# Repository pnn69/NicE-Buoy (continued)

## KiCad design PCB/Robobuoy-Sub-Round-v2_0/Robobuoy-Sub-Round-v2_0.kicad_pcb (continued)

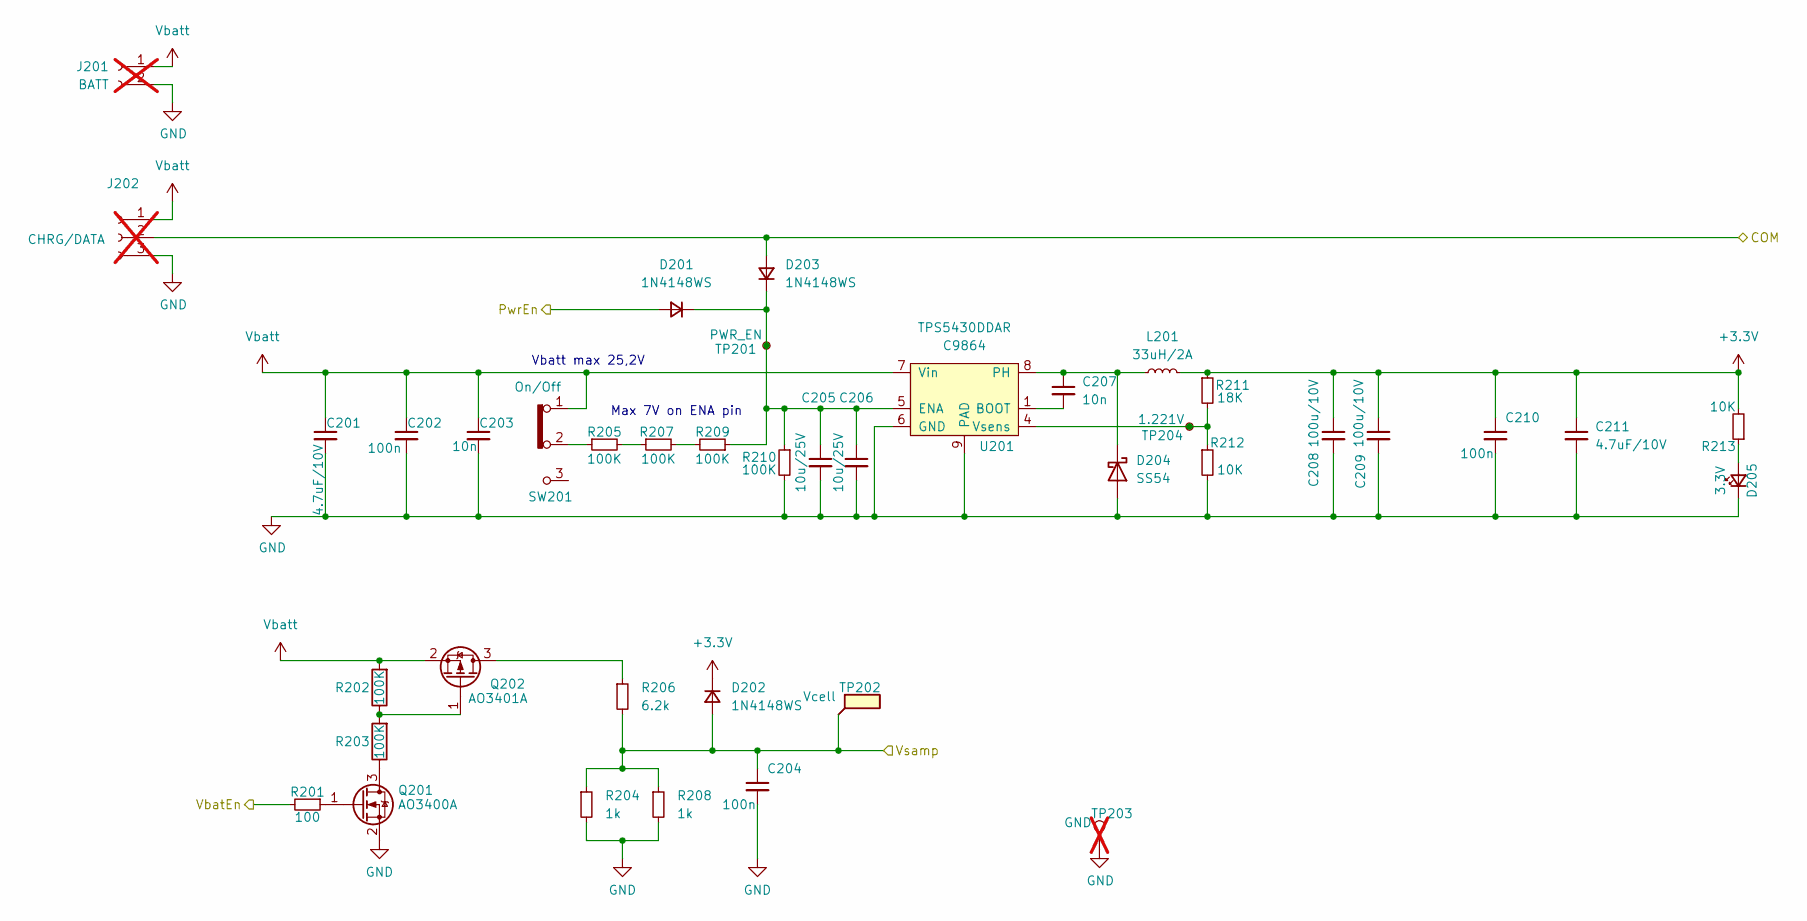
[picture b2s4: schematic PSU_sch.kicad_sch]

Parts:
C201, C211: 4.7uF/10V; C_1206_(1.6); LCSC C29823
C202, C204, C210: 100n; C_0603; LCSC C14663
C203, C207: 10n; C_0603; LCSC C57112
C205, C206: 10u/25V; C_0805; LCSC C15850
C208, C209: 100u/10V; C_1210_3225Metric; LCSC C23742
D201, D202, D203: 1N4148WS; D_SOD-323_1.8x1.4x1.15; LCSC C2128
D204: SS54; D_SMA; LCSC C22452
D205: 3.3V; LED_0805; LCSC C2297
J201: BATT; SolderWire-0.75sqmm_1x02_P4.8mm_D1.25mm_OD2.3mm; not fitted
J202: CHRG/DATA; SolderWire-0.75sqmm_1x03_P4.8mm_D1.25mm_OD2.3mm; not fitted
L201: 33uH/2A; L_6.6x7.0mm; LCSC C177245
Q201: AO3400A; SOT-23; LCSC C20917
Q202: AO3401A; SOT-23; LCSC C15127
R201: 100; R_0603; LCSC C22775
R202, R203: 100K; R_0603; Farnell 2331736
R204, R208: 1k; R_0603; LCSC C21190
R205, R207, R209, R210: 100K; R_0603; LCSC C25804
R206: 6.2k; R_0603; LCSC C25804
R211: 18K; R_0603; LCSC C25810
R212, R213: 10K; R_0603; LCSC C25804
SW201: On/Off; Header_1x03_P2.54_Male; LCSC C2937625
TP201: PWR_EN; Testpad_1
TP202: Vcell; Testpad_1
TP203: GND; TestPoint_Loop_D2.54mm_Drill1.5mm_Beaded; not fitted
TP204: 1.221V; Testpad_1
U201: TPS5430DDAR; HTSOP-8-1EP_3.9x4.9mm_P1.27mm_EP2.4x3.2mm_ThermalVias; LCSC C9864

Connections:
+3.3V: C208.1, C209.1, C210.1, C211.1, D202.1 (K), L201.2, R211.1, R213.2; also elsewhere on the board
/CPU/COM: D203.2 (A), J202.2; also elsewhere on the board
/CPU/PwrEn: D201.2 (A); also elsewhere on the board
/CPU/VbatEn: R201.2; also elsewhere on the board
/CPU/Vsamp: C204.1, D202.2 (A), R204.1, R206.2, R208.1, TP202.1; also elsewhere on the board
GND: C201.2, C202.2, C203.2, C204.2, C205.2, C206.2, C208.2, C209.2, C210.2, C211.2, D204.2 (A), D205.1 (K), J201.2, J202.3, Q201.2 (S), R204.2, R208.2, R210.2, R212.2, TP203.1, U201.6 (GND), U201.9 (PAD); also elsewhere on the board
unnamed: C205.1, C206.1, D201.1 (K), D203.1 (K), R209.1, R210.1, TP201.1, U201.5 (ENA)
unnamed: C207.1, D204.1 (K), L201.1, U201.8 (PH)
unnamed: D205.2 (A), R213.1
unnamed: Q201.3 (D), R203.1
unnamed: Q201.1 (G), R201.1
unnamed: Q202.3 (D), R206.1
unnamed: Q202.1 (G), R202.1, R203.2
unnamed: R205.1, SW201.2
unnamed: R205.2, R207.1
unnamed: R207.2, R209.2
unnamed: C207.2, U201.1 (BOOT)
unnamed: R211.2, R212.1, TP204.1, U201.4 (Vsens)
Vbatt: C201.1, C202.1, C203.1, J201.1, J202.1, Q202.2 (S), R202.2, SW201.1, U201.7 (Vin); also elsewhere on the board

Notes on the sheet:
Vbatt max 25,2V
Max 7V on ENA pin

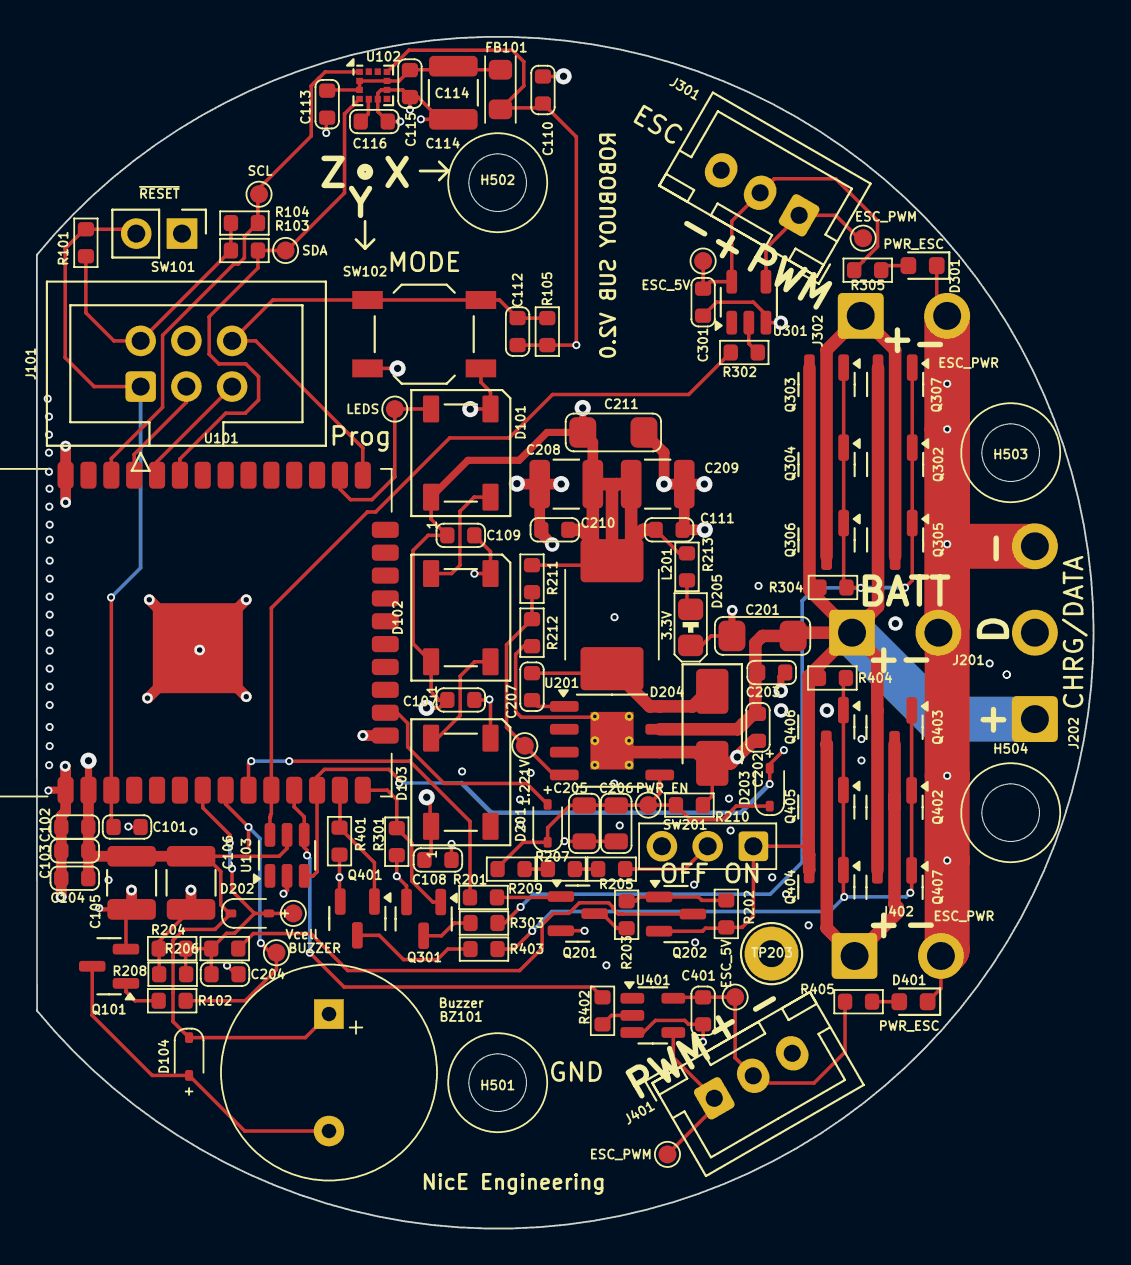
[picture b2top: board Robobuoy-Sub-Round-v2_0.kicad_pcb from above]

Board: 4 copper layers, 58.7 x 66.2 mm, 120 parts (0 on the bottom side), 51 nets.

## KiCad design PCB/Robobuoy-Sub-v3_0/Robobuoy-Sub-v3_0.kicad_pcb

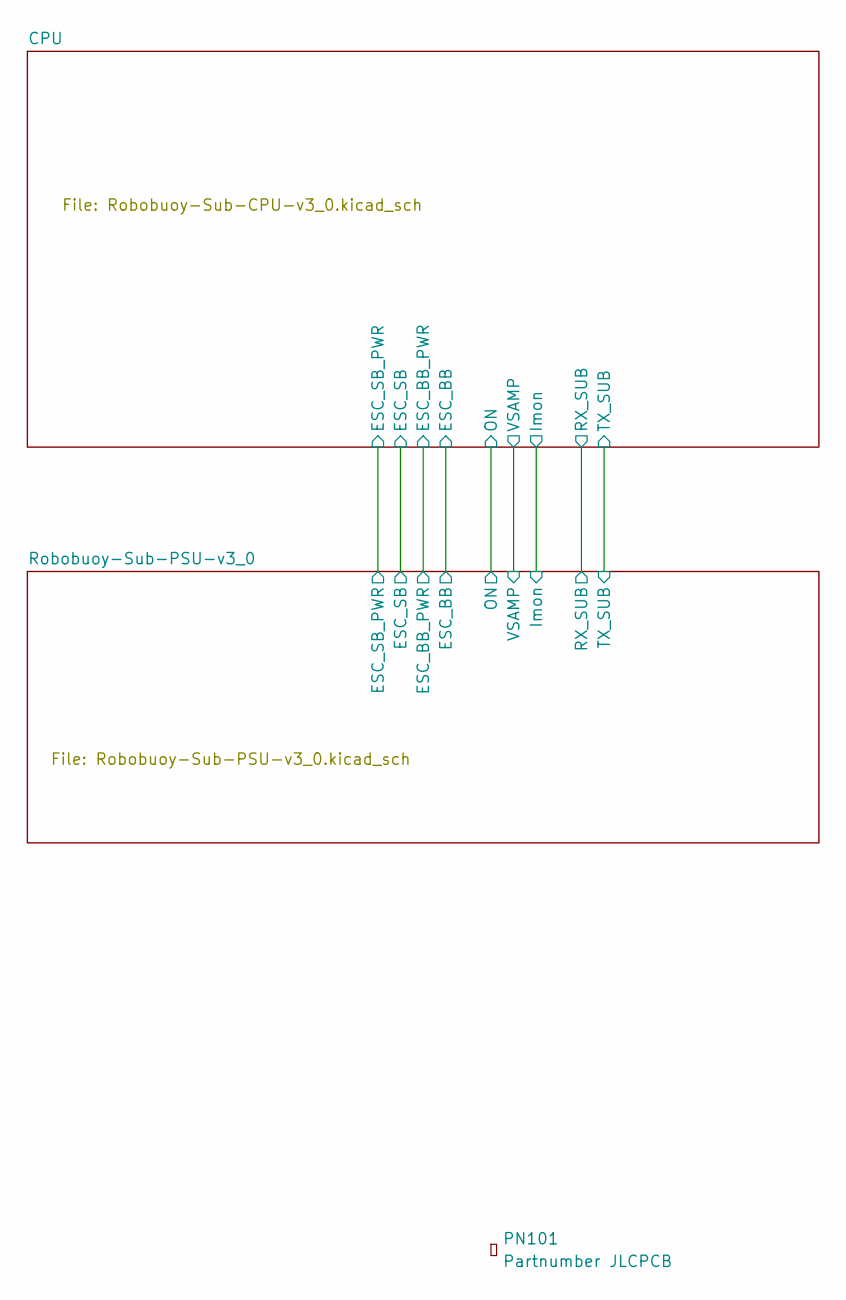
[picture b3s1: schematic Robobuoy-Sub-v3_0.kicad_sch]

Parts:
PN101: Partnumber JLCPCB; Part_Num_JLCPCB

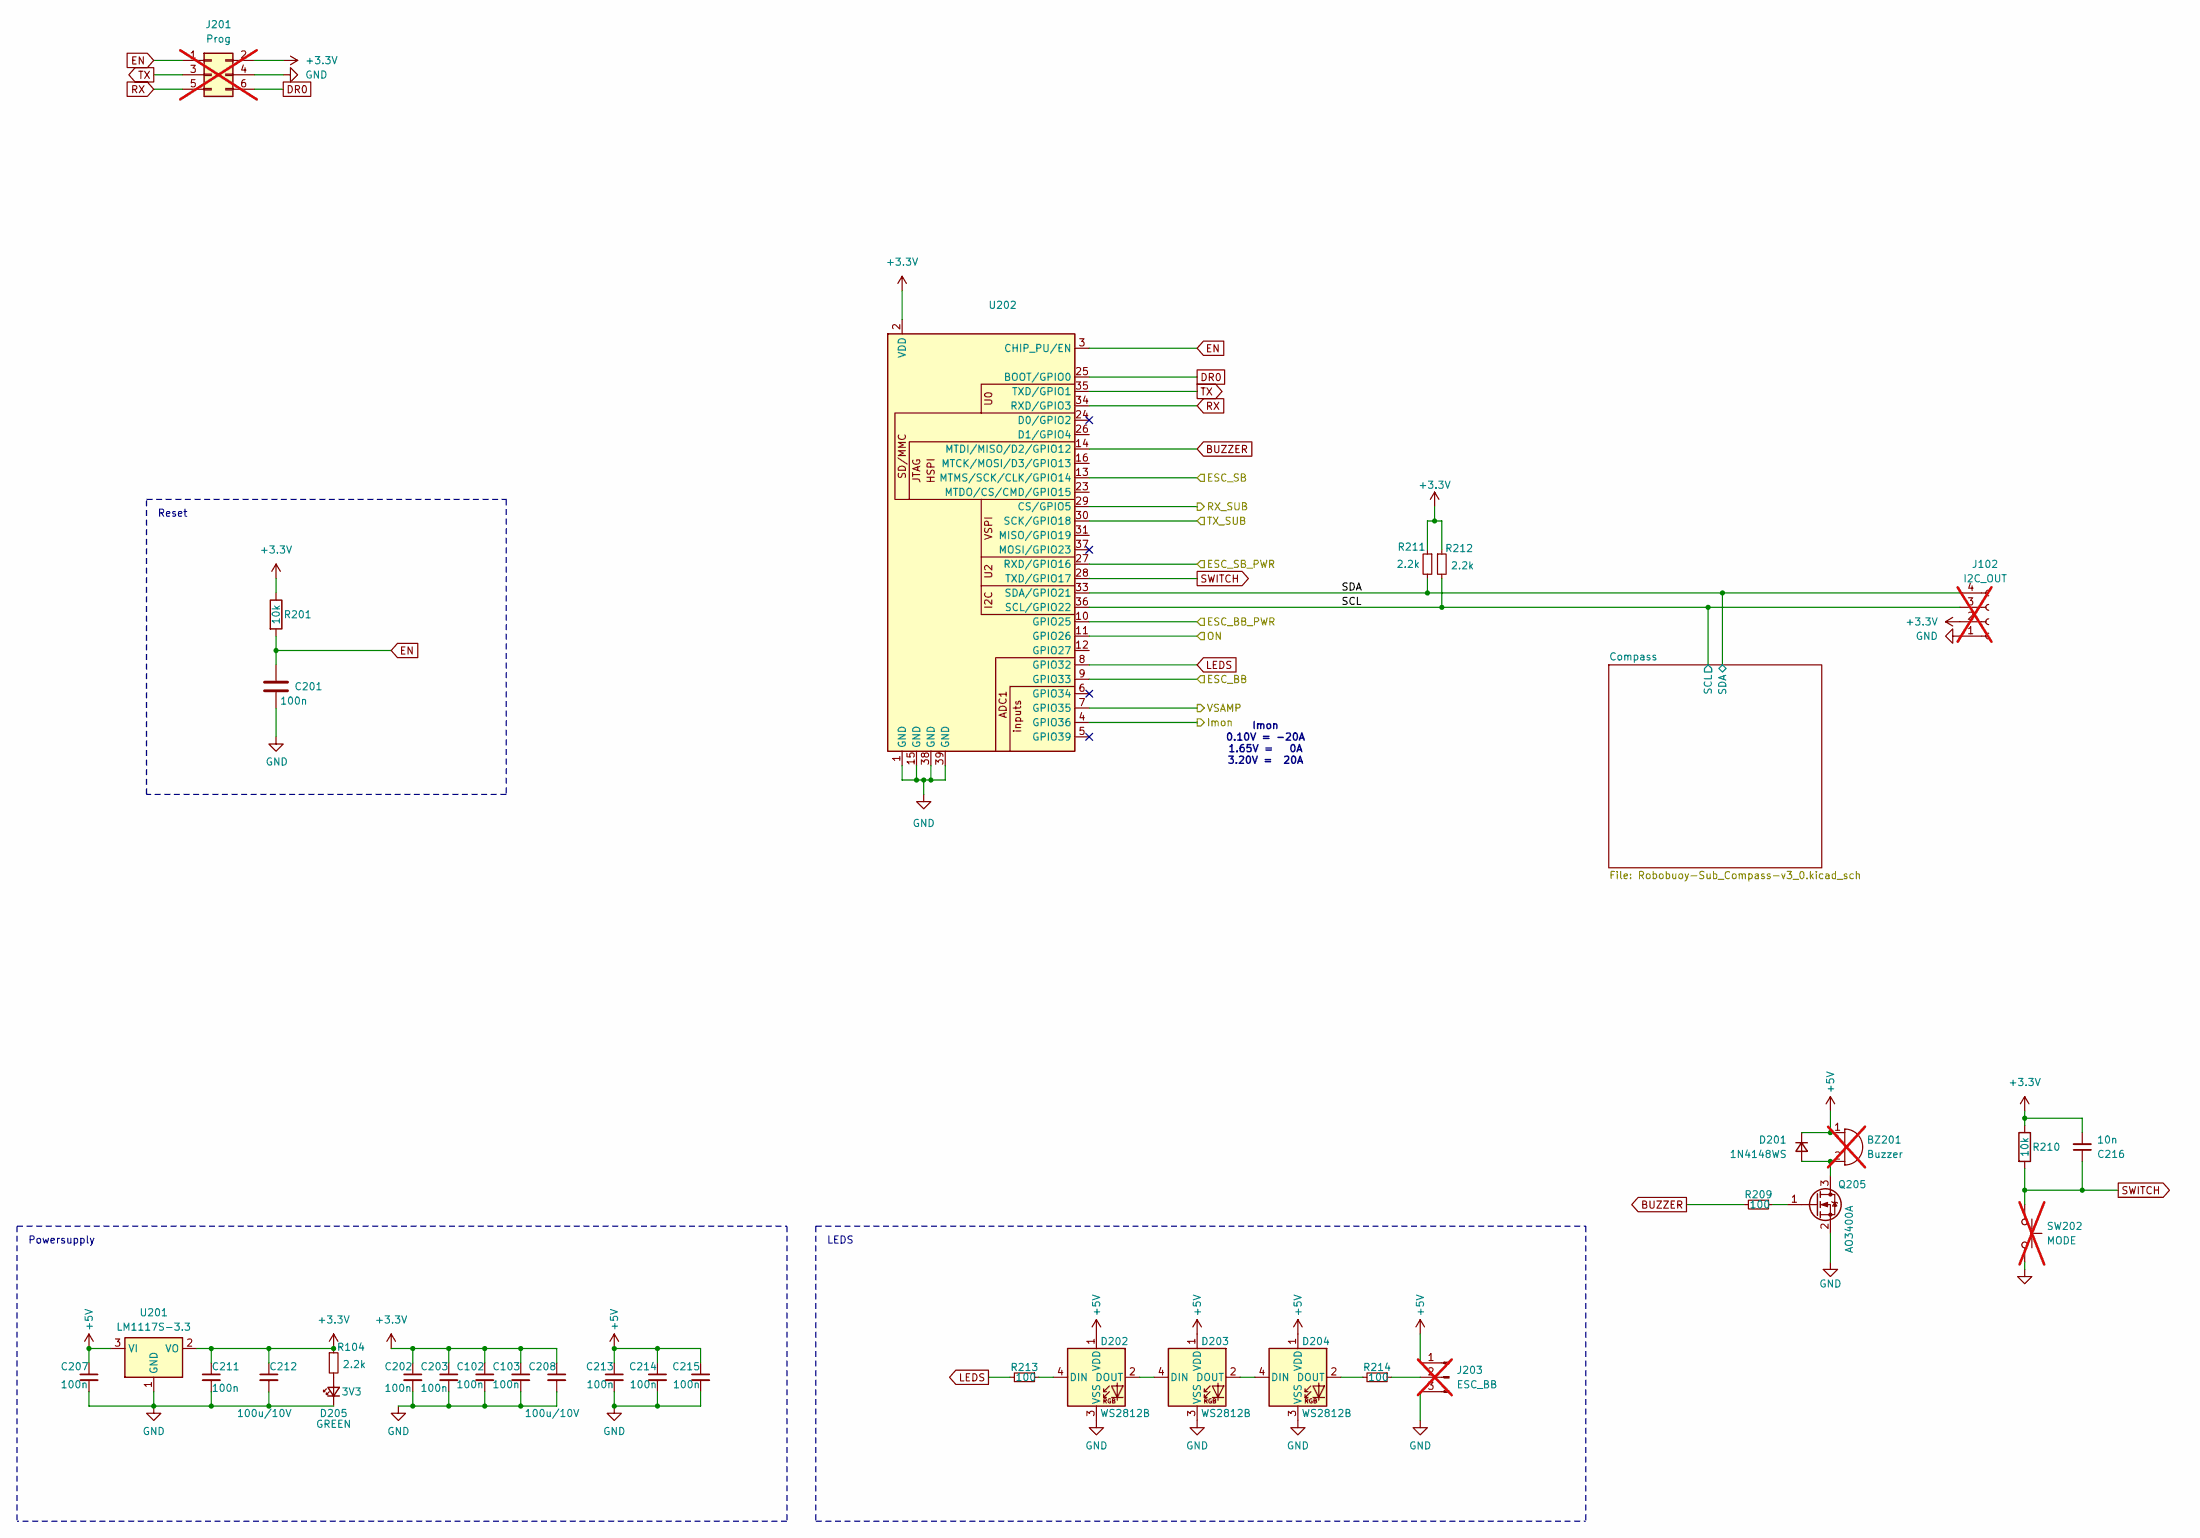
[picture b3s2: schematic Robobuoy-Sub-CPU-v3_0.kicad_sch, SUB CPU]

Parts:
BZ201: Buzzer; Header_1x02_P2.54_Jumper; LCSC C968749; not fitted
C102, C103, C201, C202, C203, C207, C211, C213, C214, C215: 100n; C_0603; LCSC C14663
C208, C212: 100u/10V; C_1210_3225Metric; LCSC C23742
C216: 10n; C_0603; LCSC C57112
D201: 1N4148WS; D_SOD-323_1.8x1.4x1.15; LCSC C2128
D202, D203, D204: WS2812B; LED_WS2812B_PLCC4_5.0x5.0mm_P3.2mm; LCSC C2843785
D205: GREEN; LED_0603_1608Metric; LCSC C12624
J102: I2C_OUT; Header_1x04_P2.54_Male; not fitted
J201: Prog; IDC-Header_2x03_P2.54mm_Vertical; LCSC C11214; not fitted
J203: ESC_BB; Header_1x03_P2.54_Male; LCSC C5341202; not fitted
Q205: AO3400A; SOT-23; LCSC C20917
R104, R211, R212: 2.2k; R_0603; LCSC C4190
R201, R210: 10k; R_0603; Farnell 2331736
R209, R213, R214: 100; R_0603; LCSC C22775
SW202: MODE; Header_1x02_P2.54_Jumper; not fitted
U201: LM1117S-3.3; SOT223; LCSC C126027
U202: ESP32-WROOM-32E_(visible_peripherals); ESP32-WROOM-32; LCSC C82899

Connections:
+3.3V: C102.1, C103.1, C202.1, C203.1, C208.1, C211.1, C212.1, C216.2, J102.2, J201.2, R104.1, R201.1, R210.1, R211.1, R212.1, U201.2 (VO), U202.2 (VDD); also elsewhere on the board
+5V: BZ201.1 (+), C207.1, C213.1, C214.1, C215.1, D201.1 (K), D202.1 (VDD), D203.1 (VDD), D204.1 (VDD), J203.1, U201.3 (VI); also elsewhere on the board
/CPU/ESC_BB: U202.9 (GPIO33); also elsewhere on the board
/CPU/ESC_BB_PWR: U202.10 (GPIO25); also elsewhere on the board
/CPU/ESC_SB: U202.13 (MTMS/SCK/CLK/GPIO14); also elsewhere on the board
/CPU/ESC_SB_PWR: U202.27 (RXD/GPIO16); also elsewhere on the board
/CPU/Imon: U202.4 (GPIO36); also elsewhere on the board
/CPU/ON: U202.11 (GPIO26); also elsewhere on the board
/CPU/RX_SUB: U202.29 (CS/GPIO5); also elsewhere on the board
/CPU/SCL: J102.3, R212.2, U202.36 (SCL/GPIO22); also elsewhere on the board
/CPU/SDA: J102.4, R211.2, U202.33 (SDA/GPIO21); also elsewhere on the board
/CPU/TX_SUB: U202.30 (SCK/GPIO18); also elsewhere on the board
/CPU/VSAMP: U202.7 (GPIO35); also elsewhere on the board
BUZZER: R209.2, U202.14 (MTDI/MISO/D2/GPIO12)
DR0: J201.6, U202.25 (BOOT/GPIO0)
EN: C201.1, J201.1, R201.2, U202.3 (CHIP_PU/EN)
GND: C102.2, C103.2, C201.2, C202.2, C203.2, C207.2, C208.2, C211.2, C212.2, C213.2, C214.2, C215.2, D202.3 (VSS), D203.3 (VSS), D204.3 (VSS), D205.1 (K), J102.1, J201.4, J203.3, Q205.2 (S), SW202.1, U201.1 (GND), U202.1 (GND), U202.15 (GND), U202.38 (GND), U202.39 (GND); also elsewhere on the board
LEDS: R213.2, U202.8 (GPIO32)
unnamed: BZ201.2 (-), D201.2 (A), Q205.3 (D)
unnamed: D202.4 (DIN), R213.1
unnamed: D202.2 (DOUT), D203.4 (DIN)
unnamed: D203.2 (DOUT), D204.4 (DIN)
unnamed: D204.2 (DOUT), R214.2
unnamed: D205.2 (A), R104.2
unnamed: J203.2, R214.1
unnamed: Q205.1 (G), R209.1
RX: J201.5, U202.34 (RXD/GPIO3)
SWITCH: C216.1, R210.2, SW202.2, U202.28 (TXD/GPIO17)
TX: J201.3, U202.35 (TXD/GPIO1)

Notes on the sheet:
Reset
Imon 0.10V = -20A 1.65V = 0A 3.20V = 20A
Powersupply
LEDS

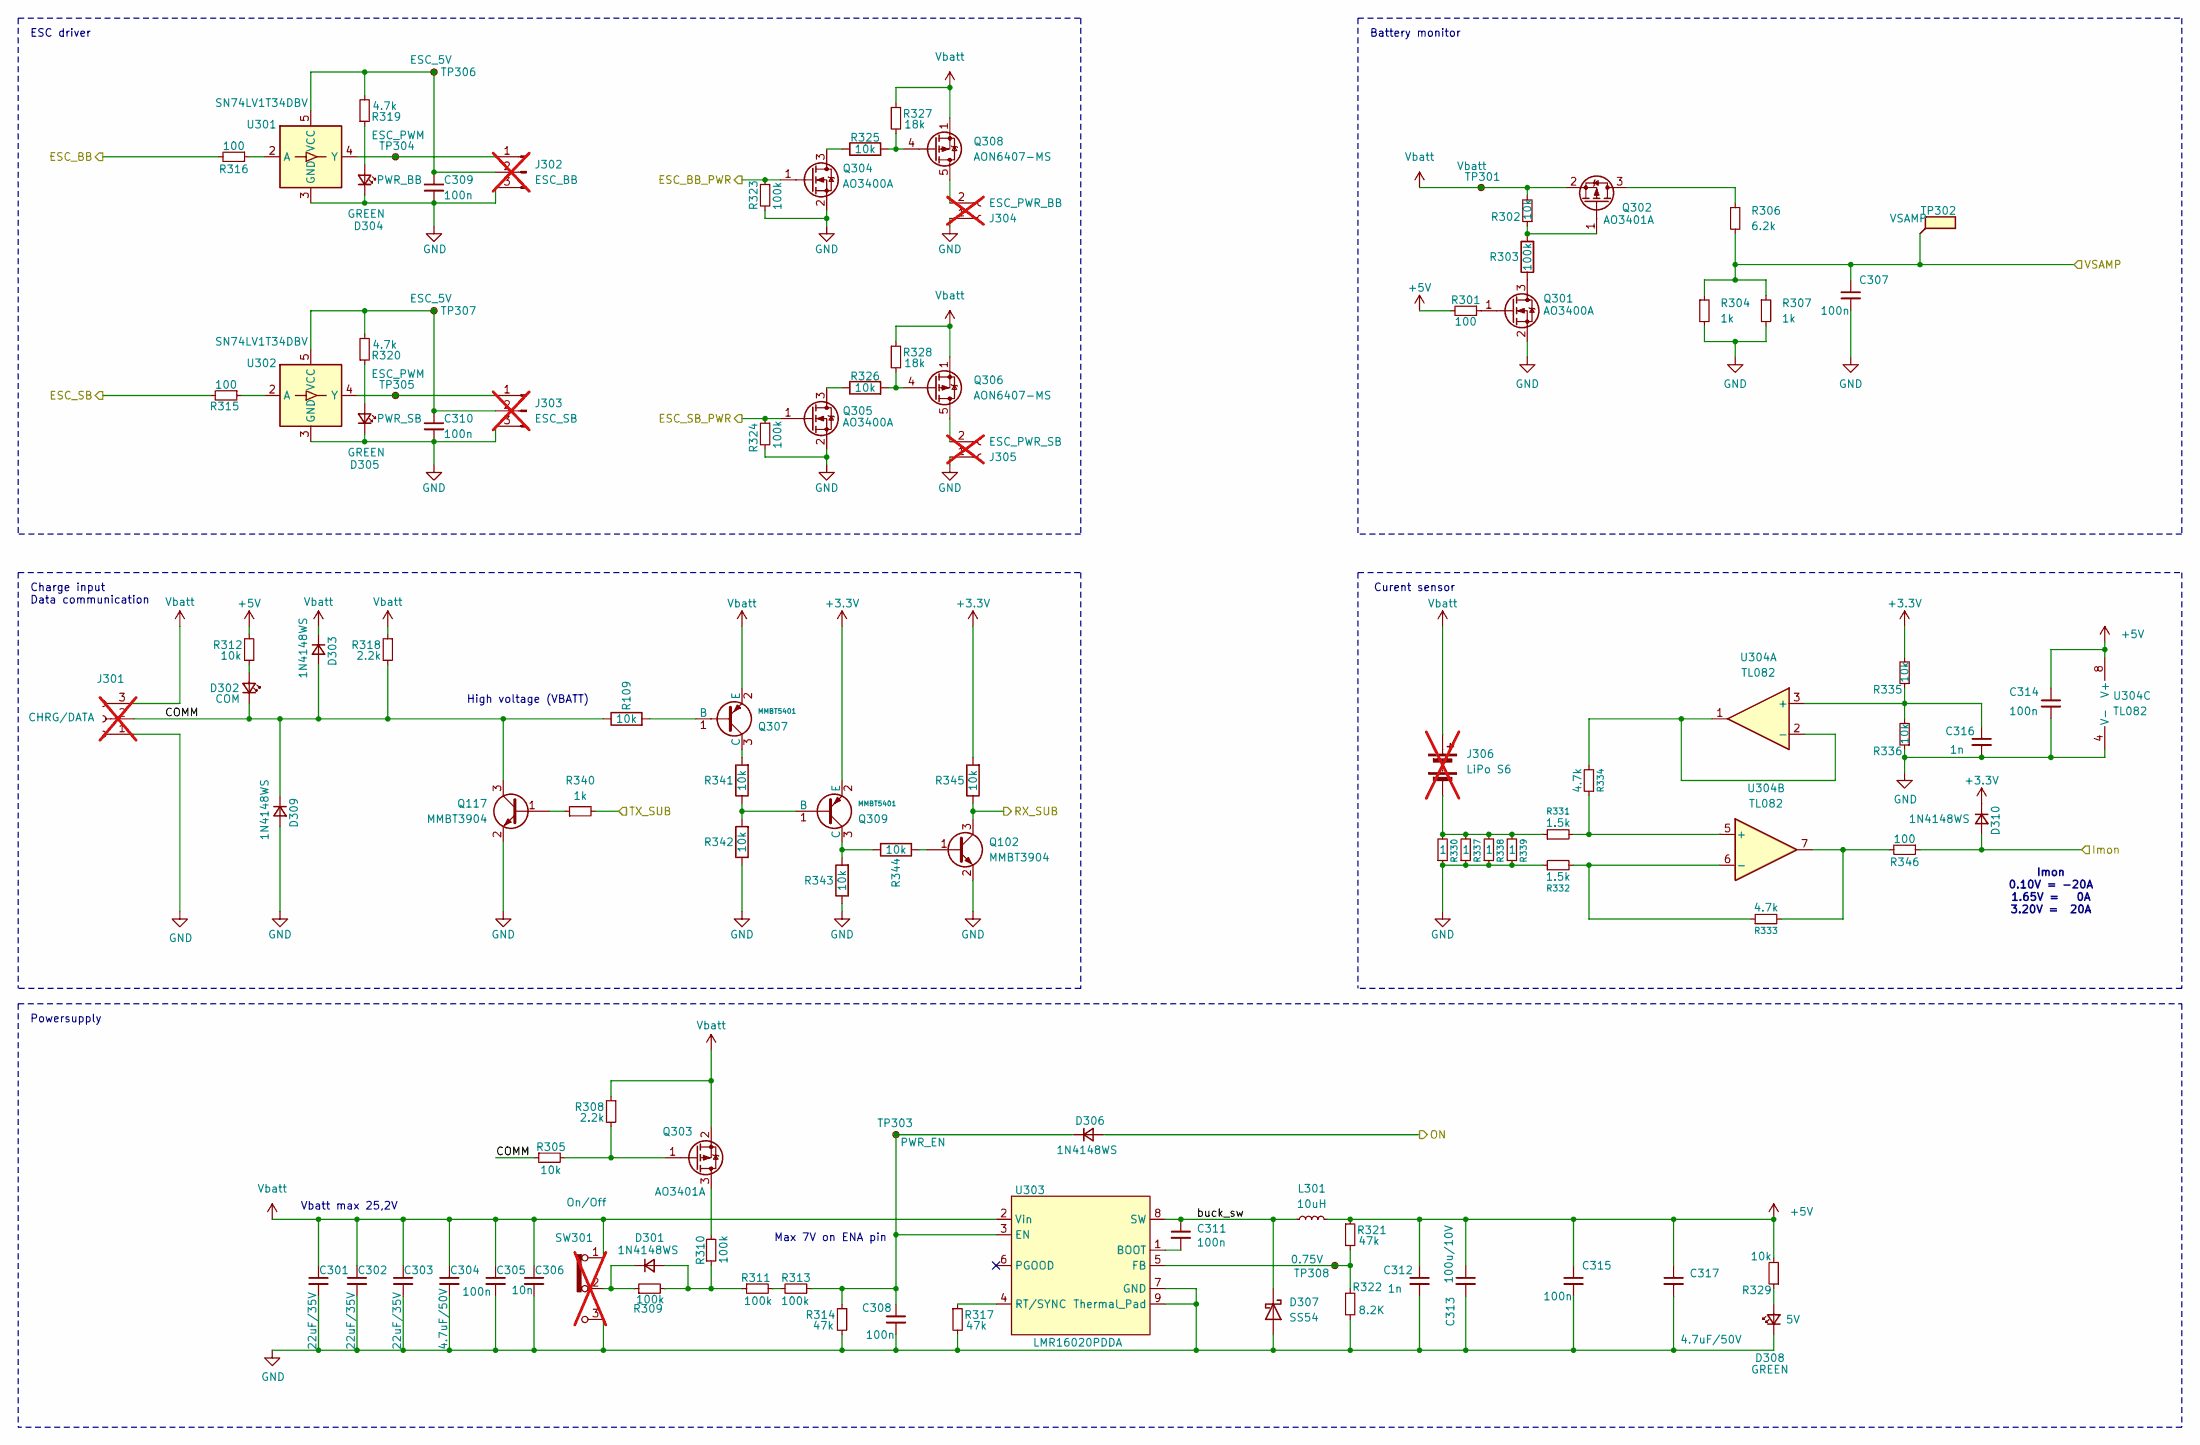
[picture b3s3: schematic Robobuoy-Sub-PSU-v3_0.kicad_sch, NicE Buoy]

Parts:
C301, C302, C303: 22uF/35V; C_1206_3216Metric; LCSC C6119969
C304, C317: 4.7uF/50V; C_1206_3216Metric; LCSC C29823
C305, C307, C308, C309, C310, C311, C314, C315: 100n; C_0603; LCSC C14663
C306: 10n; C_0603; LCSC C57112
C312, C316: 1n; C_0603; LCSC C1588
C313: 100u/10V; C_1210_3225Metric; LCSC C23742
D301, D303, D306, D309, D310: 1N4148WS; D_SOD-323_1.8x1.4x1.15; LCSC C2128
D302: COM; LED_0603_1608Metric; LCSC C2286
D304, D305, D308: GREEN; LED_0603_1608Metric; LCSC C12624
D307: SS54; D_SMA; LCSC C22452
J301: CHRG/DATA; RoundWire_1x03_P5.50mm_Vertical; LCSC C19268044; not fitted
J302: ESC_BB; JST_XH_B3B-XH-A_1x03_P2.50mm_Vertical; LCSC C5341202; not fitted
J303: ESC_SB; JST_XH_B3B-XH-A_1x03_P2.50mm_Vertical; LCSC C5341202; not fitted
J304: ESC_PWR_BB; AMASS_XT30U-M_1x02_P5.0mm_Vertical; LCSC C428722; not fitted
J305: ESC_PWR_SB; AMASS_XT30U-M_1x02_P5.0mm_Vertical; LCSC C428722; not fitted
J306: LiPo S6; not fitted
L301: 10uH; L_6.6x7.0mm; LCSC C2894722
Q102, Q117: MMBT3904; SOT-23
Q301, Q304, Q305: AO3400A; SOT-23; LCSC C20917
Q302, Q303: AO3401A; SOT-23; LCSC C15127
Q306, Q308: AON6407-MS; AO_DFN-8-1EP_5.55x5.2mm_P1.27mm_EP4.12x4.6mm; LCSC C17702953
Q307, Q309: MMBT5401; Q_SOT-23; Part MMBT5401; LCSC C7420356
R109, R341, R342, R343, R344, R345: 10k; R_0603; Farnell 2331736
R301, R315, R316, R346: 100; R_0603; LCSC C22775
R302, R305, R312, R325, R326, R329, R335, R336: 10k; R_0603; LCSC C25804
R303, R309, R310, R311, R313, R323, R324: 100k; R_0603; LCSC C25803
R304, R307, R340: 1k; R_0603; LCSC C21190
R306: 6.2k; R_0603; LCSC C4260
R308, R318: 2.2k; R_0603; LCSC C4190
R314, R317, R321: 47k; R_0603; LCSC C25819
R319, R320, R333, R334: 4.7k; R_0603; LCSC C4177
R322: 8.2K; R_0603; LCSC C25981
R327, R328: 18k; R_0603; LCSC C25810
R330, R337, R338, R339: 1; R_2512_6332Metric_Pad1.40x3.35mm_HandSolder
R331, R332: 1.5k; R_0603
SW301: On/Off; Header_1x03_P2.54_Male; LCSC C2937625; not fitted
TP301: Vbatt; Testpad_1.4
TP302: VSAMP; Testpad_1
TP303: PWR_EN; Testpad_1.4
TP304: ESC_PWM; Testpad_1
TP305: ESC_PWM; Testpad_1.4
TP306: ESC_5V; Testpad_1
TP307: ESC_5V; Testpad_1.4
TP308: 0.75V; Testpad_1.4
U301, U302: SN74LV1T34DBV; SOT-23-5; LCSC C100024
U303: LMR16020PDDA; SOIC-8-1EP_3.9x4.9mm_P1.27mm_EP2.41x3.81mm_ThermalVias; LCSC C190006
U304: TL082; SO-8_3.9x4.9mm_P1.27mm

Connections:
+3.3V: D310.1 (K), Q309.2 (E), R335.2, R345.2; also elsewhere on the board
+5V: C312.1, C313.1, C314.1, C315.1, C317.1, L301.2, R301.2, R312.2, R321.1, R329.2, U304.8 (V+); also elsewhere on the board
/CPU/ESC_BB: R316.2; also elsewhere on the board
/CPU/ESC_BB_PWR: Q304.1 (G), R323.1; also elsewhere on the board
/CPU/ESC_SB: R315.2; also elsewhere on the board
/CPU/ESC_SB_PWR: Q305.1 (G), R324.1; also elsewhere on the board
/CPU/Imon: D310.2 (A), R346.1; also elsewhere on the board
/CPU/ON: D306.2 (A); also elsewhere on the board
/CPU/RX_SUB: Q102.3 (C), R345.1; also elsewhere on the board
/CPU/TX_SUB: R340.2; also elsewhere on the board
/CPU/VSAMP: C307.1, R304.1, R306.2, R307.1, TP302.1; also elsewhere on the board
/Robobuoy-Sub-PSU-v3_0/COMM: D302.1 (K), D303.2 (A), D309.1 (K), J301.2, Q117.3 (C), R109.1, R305.1, R318.2
/Robobuoy-Sub-PSU-v3_0/buck_sw: C311.1, D307.1 (K), L301.1, U303.8 (SW)
GND: C301.2, C302.2, C303.2, C304.2, C305.2, C306.2, C307.2, C308.2, C309.2, C310.2, C312.2, C313.2, C314.2, C315.2, C316.2, C317.2, D304.1 (K), D305.1 (K), D307.2 (A), D308.1 (K), D309.2 (A), J301.1, J302.3, J303.3, J304.1, J305.1, Q102.2 (E), Q117.2 (E), Q301.2 (S), Q304.2 (S), Q305.2 (S), R304.2, R307.2, R314.2, R317.2, R322.2, R323.2, R324.2, R330.1, R332.1, R336.1, R337.1, R338.1, R339.1, R342.1, R343.1, SW301.3, U301.3 (GND), U302.3 (GND), U303.7 (GND), U303.9 (Thermal_Pad), U304.4 (V-); also elsewhere on the board
unnamed: D301.2 (A), R309.2, R310.1, R311.1
unnamed: D301.1 (K), R309.1, SW301.2
unnamed: D302.2 (A), R312.1
unnamed: D304.2 (A), R319.1
unnamed: D305.2 (A), R320.1
unnamed: C308.1, D306.1 (K), R313.1, R314.1, TP303.1, U303.3 (EN)
unnamed: D308.2 (A), R329.1
unnamed: J302.1, TP304.1, U301.4 (Y)
unnamed: C309.1, J302.2, R319.2, TP306.1, U301.5 (VCC)
unnamed: J303.1, TP305.1, U302.4 (Y)
unnamed: C310.1, J303.2, R320.2, TP307.1, U302.5 (VCC)
unnamed: J304.2, Q308.5 (D)
unnamed: J305.2, Q306.5 (D)
unnamed: J306.1 (-), R330.2, R331.1, R337.2, R338.2, R339.2
unnamed: Q102.1 (B), R344.1
unnamed: Q117.1 (B), R340.1
unnamed: Q301.3 (D), R303.1
unnamed: Q301.1 (G), R301.1
unnamed: Q302.3 (D), R306.1
unnamed: Q302.1 (G), R302.1, R303.2
unnamed: Q303.3 (D), R310.2
unnamed: Q303.1 (G), R305.2, R308.2
unnamed: Q304.3 (D), R325.1
unnamed: Q305.3 (D), R326.1
unnamed: Q306.4 (G), R326.2, R328.2
unnamed: Q307.1 (B), R109.2
unnamed: Q307.3 (C), R341.2
unnamed: Q308.4 (G), R325.2, R327.2
unnamed: Q309.1 (B), R341.1, R342.2
unnamed: Q309.3 (C), R343.2, R344.2
unnamed: R311.2, R313.2
unnamed: R333.2, R346.2, U304.7
unnamed: R316.1, U301.2 (A)
unnamed: R315.1, U302.2 (A)
unnamed: C311.2, U303.1 (BOOT)
unnamed: R321.2, R322.1, TP308.1, U303.5 (FB)
unnamed: R317.1, U303.4 (RT/SYNC)
unnamed: C316.1, R335.1, R336.2, U304.3 (+)
unnamed: R334.2, U304.1, U304.2 (-)
unnamed: R331.2, R334.1, U304.5 (+)
unnamed: R332.2, R333.1, U304.6 (-)
Vbatt: C301.1, C302.1, C303.1, C304.1, C305.1, C306.1, D303.1 (K), J301.3, J306.2 (+), Q302.2 (S), Q303.2 (S), Q306.1 (S), Q306.2 (S), Q306.3 (S), Q307.2 (E), Q308.1 (S), Q308.2 (S), Q308.3 (S), R302.2, R308.1, R318.1, R327.1, R328.1, SW301.1, TP301.1, U303.2 (Vin)

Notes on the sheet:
ESC driver
Battery monitor
Max 7V on ENA pin
Imon 0.10V = -20A 1.65V = 0A 3.20V = 20A
Charge input Data communication
High voltage (VBATT)
Powersupply
Curent sensor
Vbatt max 25,2V

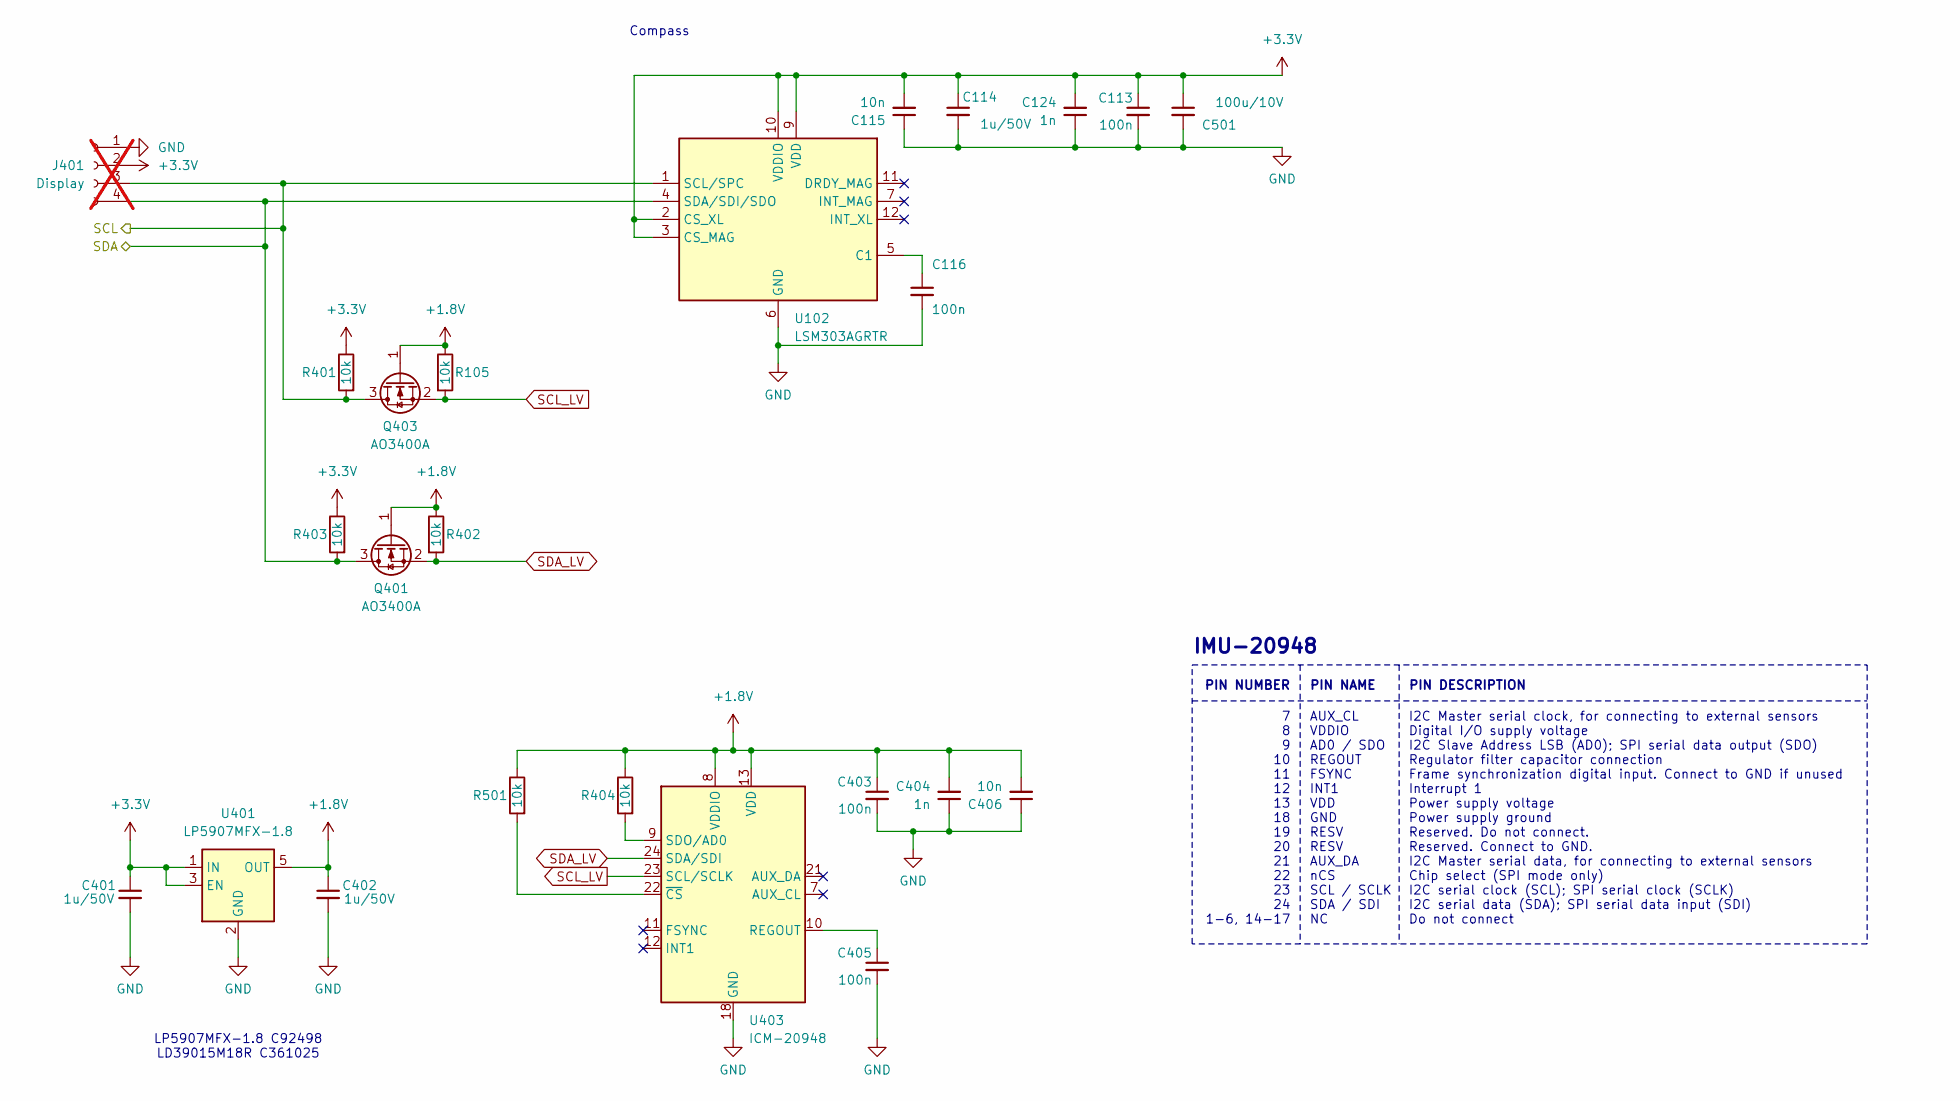
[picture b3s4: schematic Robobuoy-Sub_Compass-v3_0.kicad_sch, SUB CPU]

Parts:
C113, C116, C403, C405: 100n; C_0603; LCSC C14663
C114, C401, C402: 1u/50V; C_0603; LCSC C15849
C115, C406: 10n; C_0603; LCSC C57112
C124, C404: 1n; C_0603; LCSC C1588
C501: 100u/10V; C_1210_3225Metric; LCSC C23742
J401: Display; Header_1x04_P2.54_Male; not fitted
Q401, Q403: AO3400A; SOT-23; LCSC C20917
R105, R401, R402, R403, R404, R501: 10k; R_0603; Farnell 2331736
U102: LSM303AGRTR; LGA-12_2x2mm_P0.5mm; LCSC C126671
U401: LP5907MFX-1.8; SOT-23-5
U403: ICM-20948; InvenSense_QFN-24_3x3mm_P0.4mm; lcsc C726001

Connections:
+1.8V: C402.1, C403.1, C404.2, C406.2, Q401.1 (G), Q403.1 (G), R105.1, R402.1, R404.1, R501.1, U401.5 (OUT), U403.8 (VDDIO), U403.13 (VDD)
+3.3V: C113.1, C114.1, C115.2, C124.2, C401.1, C501.1, J401.2, R401.1, R403.1, U102.2 (CS_XL), U102.3 (CS_MAG), U102.9 (VDD), U102.10 (VDDIO), U401.1 (IN), U401.3 (EN); also elsewhere on the board
/CPU/SCL: J401.3, Q403.3 (D), R401.2, U102.1 (SCL/SPC); also elsewhere on the board
/CPU/SDA: J401.4, Q401.3 (D), R403.2, U102.4 (SDA/SDI/SDO); also elsewhere on the board
GND: C113.2, C114.2, C115.1, C116.2, C124.1, C401.2, C402.2, C403.2, C404.1, C405.2, C406.1, C501.2, J401.1, U102.6 (GND), U102.8 (GND), U401.2 (GND), U403.18 (GND), U403.20 (GND); also elsewhere on the board
unnamed: C116.1, U102.5 (C1)
unnamed: C405.1, U403.10 (REGOUT)
unnamed: R404.2, U403.9 (SDO/AD0)
unnamed: R501.2, U403.22 (~CS)
SCL_LV: Q403.2 (S), R105.2, U403.23 (SCL/SCLK)
SDA_LV: Q401.2 (S), R402.2, U403.24 (SDA/SDI)

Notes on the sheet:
LP5907MFX-1.8 C92498 LD39015M18R C361025
PIN DESCRIPTION
PIN NAME
AUX_CL VDDIO AD0 / SDO REGOUT FSYNC INT1 VDD GND RESV RESV AUX_DA nCS SCL / SCLK SDA / SDI NC
I2C Master serial clock, for connecting to external sensors Digital I/O supply voltage I2C Slave Address LSB (AD0); SPI serial data output (SDO) Regulator filter capacitor connection Frame synchronization digital input. Connect to GND if unused Interrupt 1 Power supply voltage Power supply ground R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
Compass
7 8 9 10 11 12 13 18 19 20 21 22 23 24 1-6, 14-17
IMU-20948
PIN NUMBER

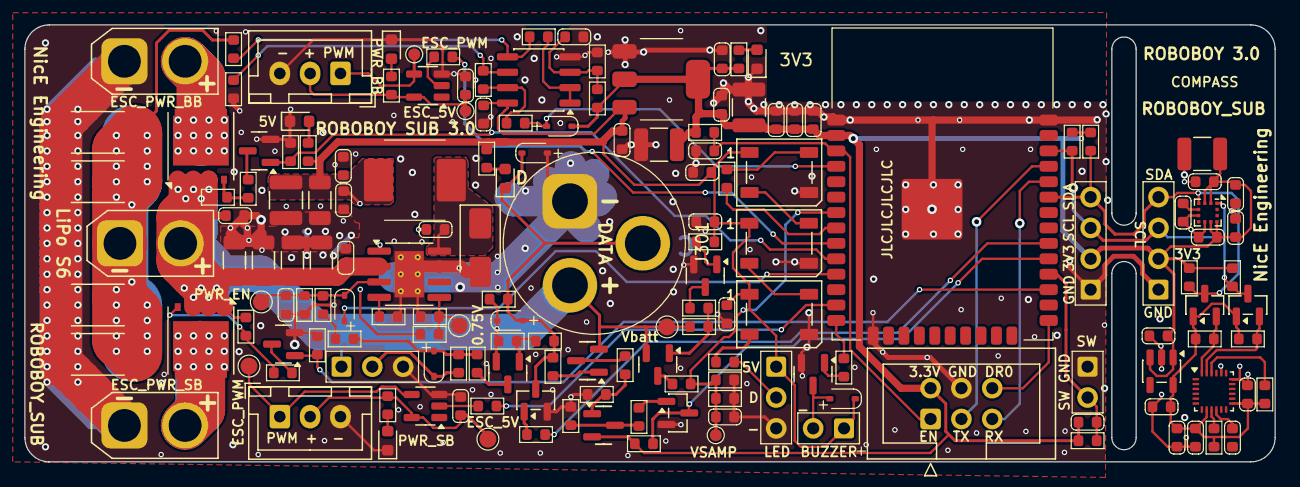
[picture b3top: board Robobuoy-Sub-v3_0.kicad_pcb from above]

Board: 4 copper layers, 103.0 x 36.0 mm, 164 parts (0 on the bottom side), 80 nets.
